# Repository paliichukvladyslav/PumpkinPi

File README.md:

# Pumpkin Pi

A small Linux single-board computer based on the Allwinner V3s.

## Hardware Specifications

| Component | Specification |
|---|---|
| SoC | Allwinner V3s (eLQFP-128) |
| CPU | Single-core ARM Cortex-A7, up to 1.2 GHz (typically 1.008 GHz) |
| RAM | 64 MiB DDR2, 400 MHz, integrated into the SoC |
| PMIC | X-Powers AXP202 |
| Power rails | 1.2V (CPU/System), 3.3V (I/O), 3.0V (Analog) |
| DDR2 power supply | 1.8V via dedicated SY8088AAC regulator |
| Flash storage | 16 MiB Winbond W25Q128JVFIQ SPI NOR (SPI0) |
| Main oscillator | 24 MHz crystal, ±10 ppm, 12 pF |
| RTC oscillator | 32.768 kHz crystal, ±20 ppm, 12.5 pF |
| Power input | USB Type-C (16-pin connector, power only) |
| Serial interfaces | UART0, UART2 |
| GPIO | 6 exposed GPIO pins (PE19–PE24) |
| Programming | Dedicated SPI NOR programming header |
| Status LED | White LED with Linux heartbeat support |
| Fan connector | 2-pin JST-PH, 3.3V |
| PCB | 4 layers, 49.9 × 45 mm |

## Software

Firmware and Linux support are yet to be implemented.

## Project Files

The repository contains the KiCad schematic, PCB layout, custom symbols, footprints, and 3D models.

If KiCad reports a missing `PumpkinPi` footprint library, reconnect `PumpkinPi.pretty` through **Preferences → Manage Footprint Libraries**.

## License

The Pumpkin Pi hardware design is licensed under
[CC BY-SA 4.0](https://creativecommons.org/licenses/by-sa/4.0/).

See Third-Party Credits for attribution of reused and adapted designs.

## Third-Party Credits

This project is partially based on and inspired by the [FunKey S Hardware](https://github.com/FunKey-Project/FunKey-S-Hardware) project.

The following elements were reused or adapted from its hardware design:

- KiCad schematic symbols for the Allwinner V3s and AXP20x PMIC.
- Crystal oscillator circuits (24 MHz and 32.768 kHz).
- SVREF reference voltage circuitry.
- DDR2 power supply design using the SY8088 regulator.
- General power management and schematic design concepts.

The original FunKey S hardware design is licensed under [CC BY-SA 4.0](https://creativecommons.org/licenses/by-sa/4.0/). Components and circuits reused in Pumpkin Pi have been adapted for this board.

Credit goes to the FunKey Project contributors for making their hardware design publicly available.

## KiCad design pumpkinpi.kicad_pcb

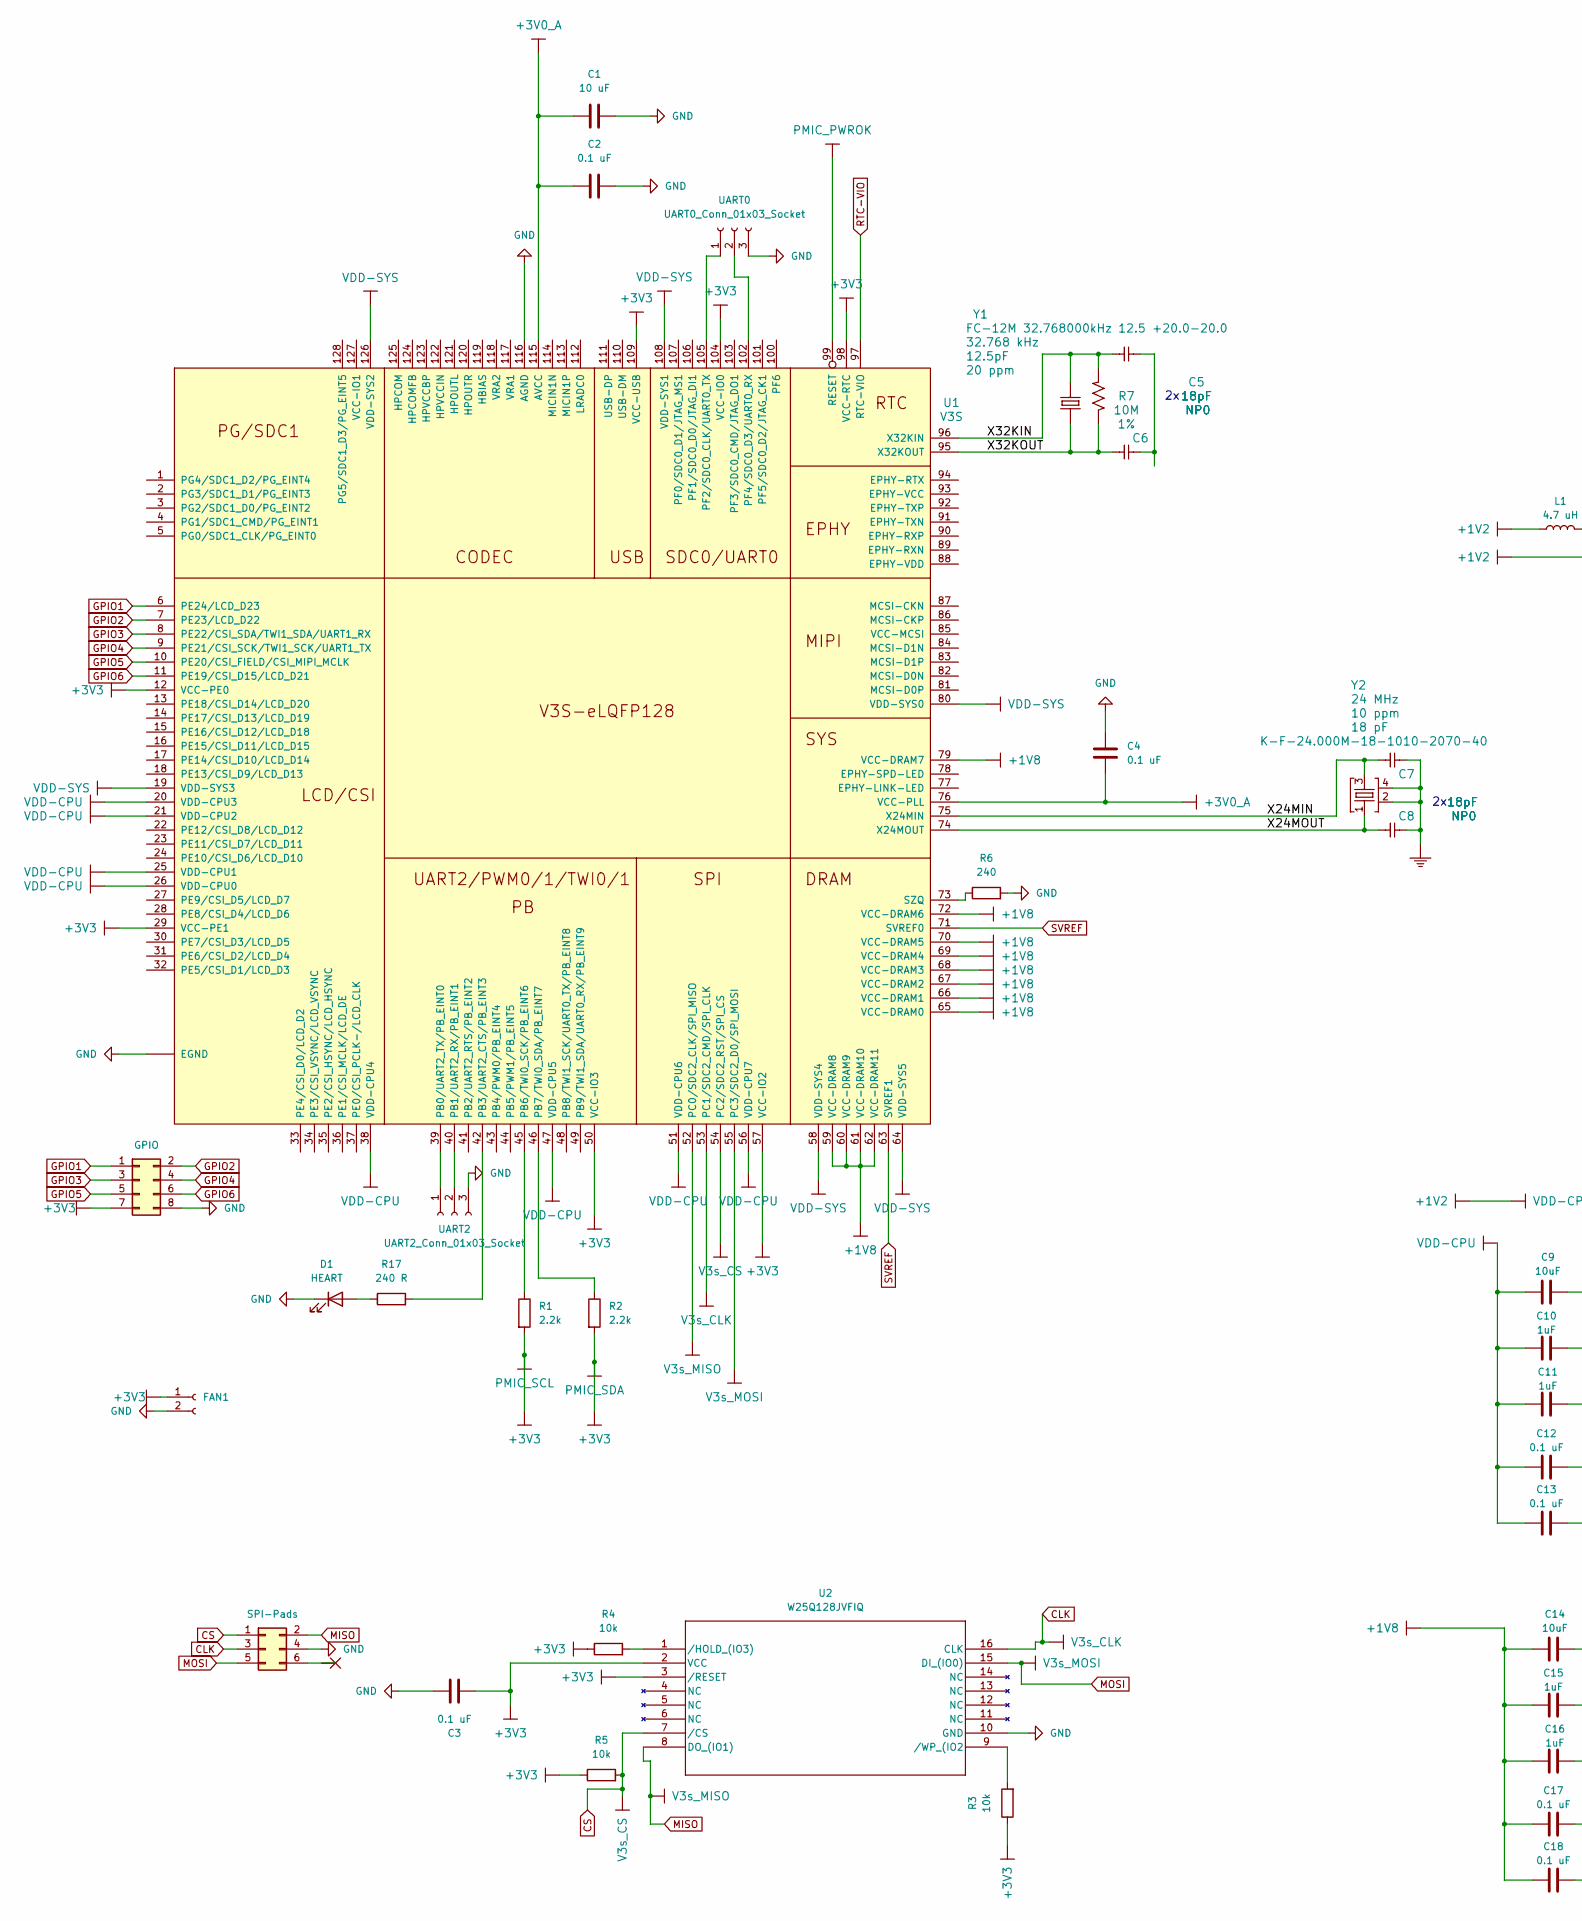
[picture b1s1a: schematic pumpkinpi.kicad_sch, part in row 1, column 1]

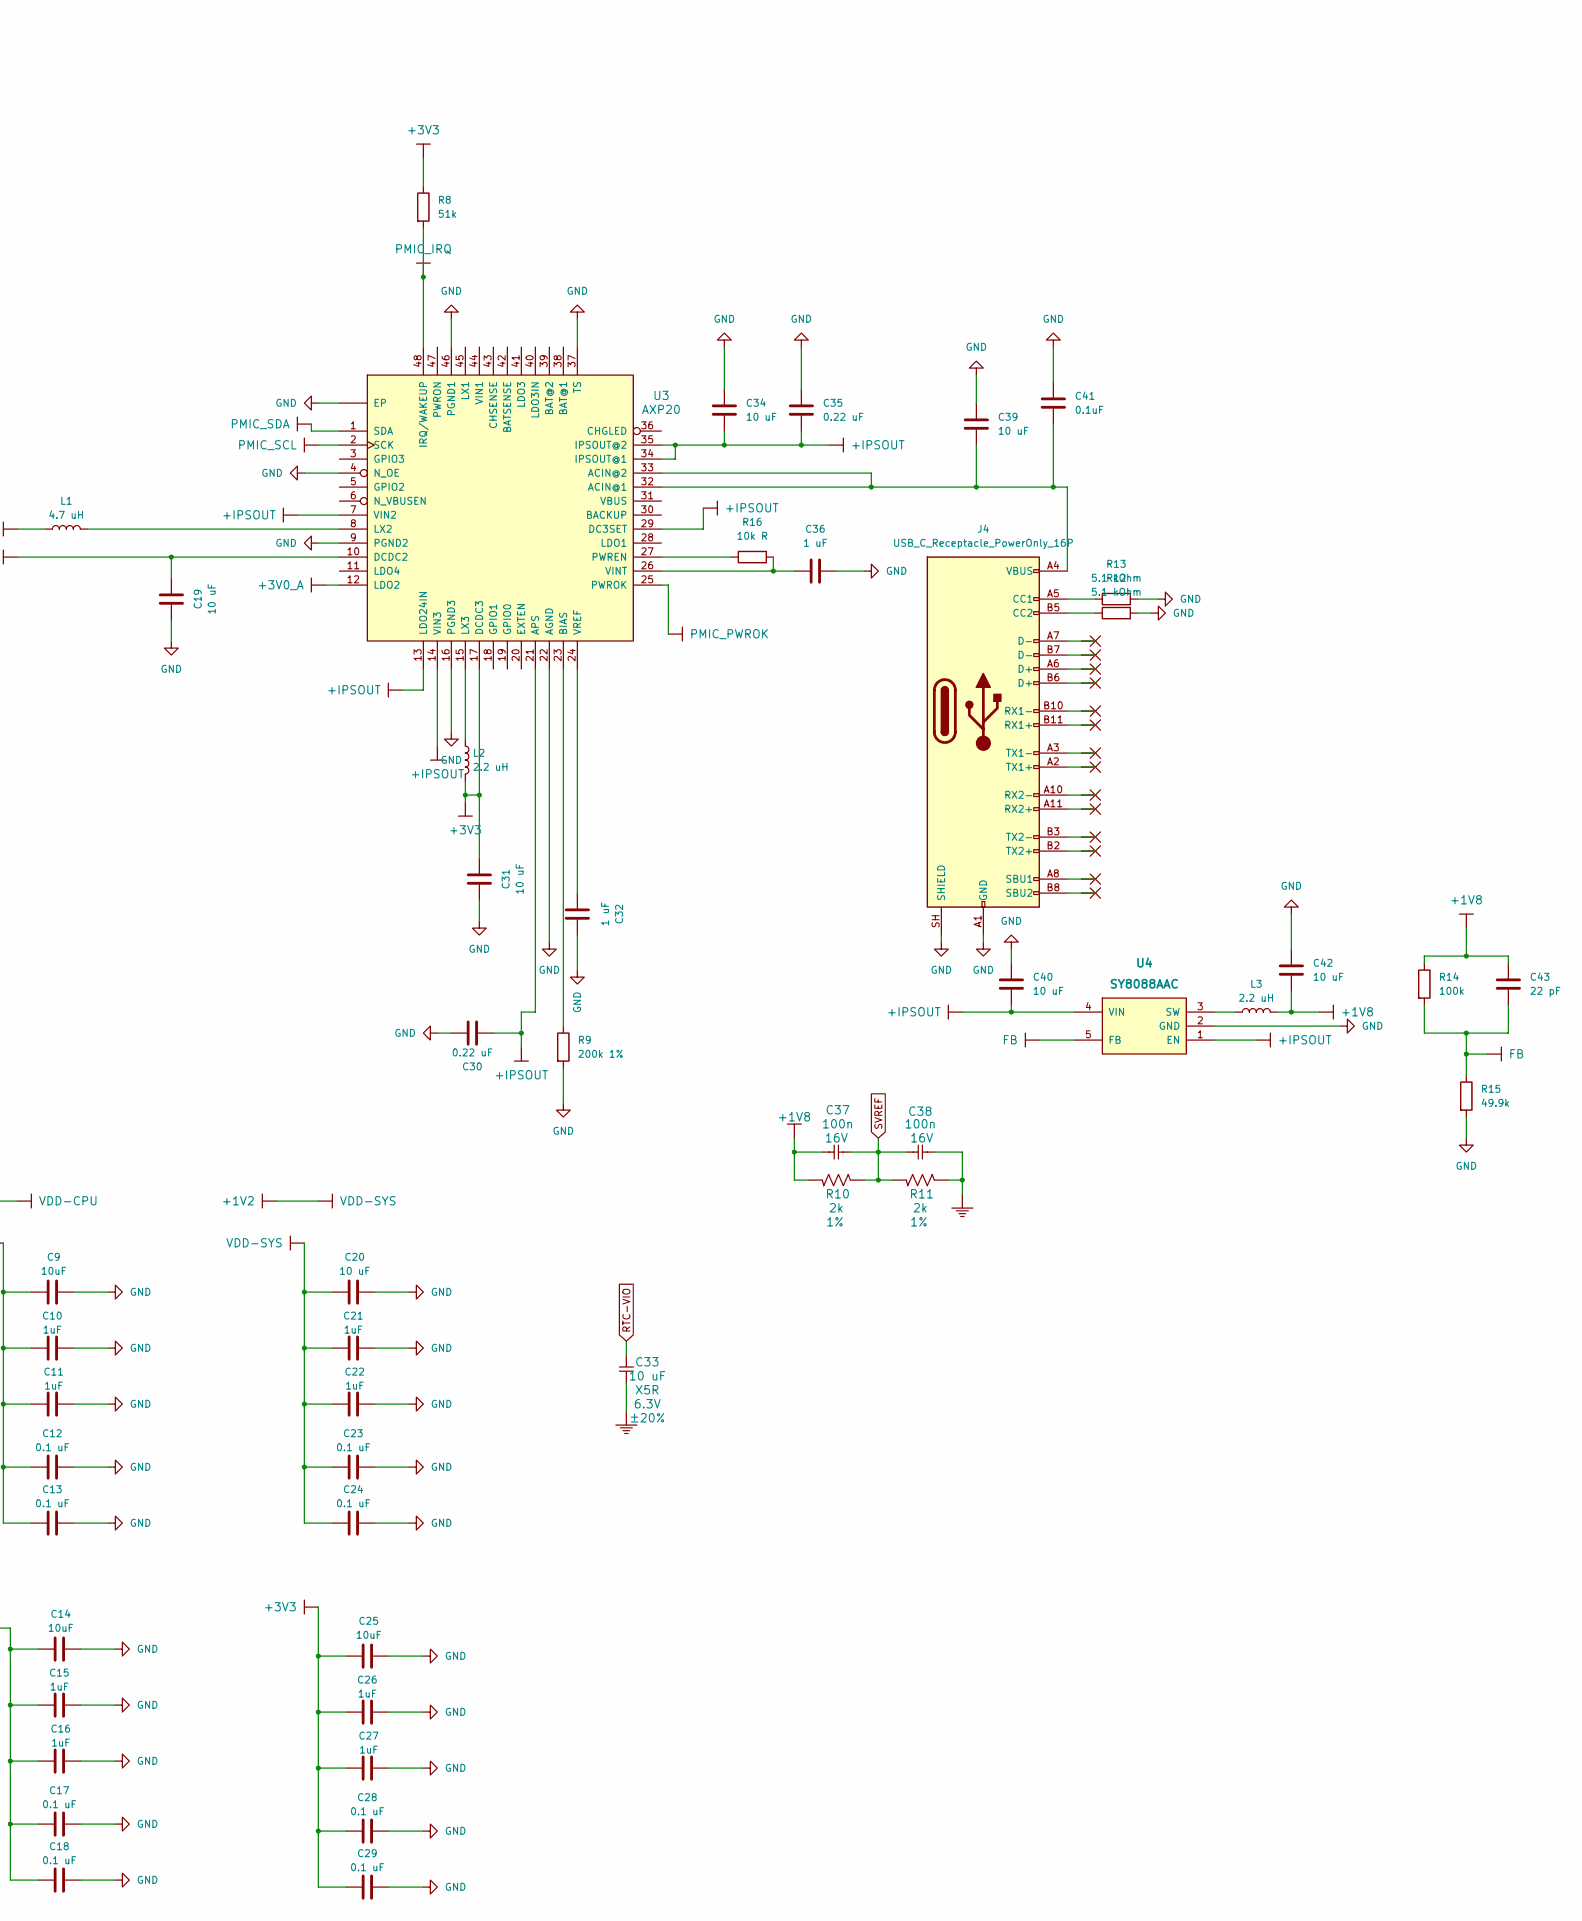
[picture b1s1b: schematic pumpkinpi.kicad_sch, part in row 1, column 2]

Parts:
C1, C19, C20, C31, C34, C39, C40, C42: 10 uF; C_0805_2012Metric
C2, C3, C4, C12, C13, C17, C18, C23, C24, C28, C29: 0.1 uF; C_0603_1608Metric
C5, C6, C7, C8: 18pF; C_0603_1608Metric; PARTNO C0402_18p_NP0_5%_CER_50V
C9: 10uF; C_0603_1608Metric
C10, C11, C15, C16, C21, C22, C26, C27: 1uF; C_0603_1608Metric
C14, C25: 10uF; C_0805_2012Metric
C30, C35: 0.22 uF; C_0603_1608Metric
C32, C36: 1 uF; C_0603_1608Metric
C33: 10 uF; C_0805_2012Metric; PARTNO C0402_10u_X5R_20%_CER_6V3
C37, C38: 100n; C_0603_1608Metric; PARTNO C0402_100n_X7R_10%_CER_16V
C41: 0.1uF; C_0603_1608Metric
C43: 22 pF; C_0603_1608Metric
D1: HEART; SUPER_BRIGHT_SMD_LED_3014
FAN1: Conn_01x02_Socket; JST_PH_B2B-PH-K_1x02_P2.00mm_Vertical
J1: GPIO; PinSocket_2x04_P2.54mm_Vertical
J4: USB_C_Receptacle_PowerOnly_16P; USB_C_Receptacle_GCT_USB4110
L1: 4.7 uH; IND_EPCOS_B82462G4_EPC
L2, L3: 2.2 uH; IND_CDRH2D14NP-2R2NC_SUM
R1, R2: 2.2k; R_0603_1608Metric
R3, R4, R5: 10k; R_0603_1608Metric
R6: 240; R_0603_1608Metric
R7: 10M; R_0603_1608Metric; PARTNO R0402_10M_1%_62.5mW
R8: 51k; R_0603_1608Metric
R9: 200k 1%; R_0603_1608Metric
R10, R11: 2k; R_0603_1608Metric; PARTNO R0402_2k_1%_62.5mW
R12, R13: 5.1 kOhm; R_0603_1608Metric
R14: 100k; R_0603_1608Metric
R15: 49.9k; R_0603_1608Metric
R16: 10k R; R_0603_1608Metric
R17: 240 R; R_0603_1608Metric
SPI-Pads1: SPI-Pads; PinHeader_1x05_P2.54mm_Vertical
U1: V3S; ELQFP-128
U2: W25Q128JVFIQ; SOIC_28JVFIQ_WIN
U3: AXP20; QFN48
U4: SY8088AAC; SOT23-5
UART0: UART0_Conn_01x03_Socket; PinSocket_1x03_P2.54mm_Vertical
UART2: UART2_Conn_01x03_Socket; PinSocket_1x03_P2.54mm_Vertical
Y1: FC-12M 32.768000kHz 12.5 +20.0-20.0; FC-12M; PARTNO FC-12M_32K768_12.5PF_20PPM
Y2: K-F-24.000M-18-1010-2070-40; CRYSTAL_32X25; PARTNO XTAL3225_4P_24M_18PF_10PPM

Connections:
+1V2: C9.2, C10.2, C11.2, C12.2, C13.2, C19.2, C20.2, C21.2, C22.2, C23.2, C24.2, L1.1, U1.19 (VDD-SYS3), U1.20 (VDD-CPU3), U1.21 (VDD-CPU2), U1.25 (VDD-CPU1), U1.26 (VDD-CPU0), U1.38 (VDD-CPU4), U1.47 (VDD-CPU5), U1.51 (VDD-CPU6), U1.56 (VDD-CPU7), U1.58 (VDD-SYS4), U1.64 (VDD-SYS5), U1.80 (VDD-SYS0), U1.108 (VDD-SYS1), U1.126 (VDD-SYS2), U3.10 (DCDC2)
+1V8: C14.2, C15.2, C16.2, C17.2, C18.2, C37.2, C42.2, C43.1, L3.2, R10.2, R14.1, U1.59 (VCC-DRAM8), U1.60 (VCC-DRAM9), U1.61 (VCC-DRAM10), U1.62 (VCC-DRAM11), U1.65 (VCC-DRAM0), U1.66 (VCC-DRAM1), U1.67 (VCC-DRAM2), U1.68 (VCC-DRAM3), U1.69 (VCC-DRAM4), U1.70 (VCC-DRAM5), U1.72 (VCC-DRAM6), U1.79 (VCC-DRAM7)
+3V0_A: C1.1, C2.1, C4.2, U1.76 (VCC-PLL), U1.115 (AVCC), U3.12 (LDO2)
+3V3: C3.1, C25.2, C26.2, C27.2, C28.2, C29.2, C31.2, FAN1.1, J1.7, L2.2, R1.2, R2.2, R3.1, R4.1, R5.1, R8.1, U1.12 (VCC-PE0), U1.29 (VCC-PE1), U1.50 (VCC-IO3), U1.57 (VCC-IO2), U1.98 (VCC-RTC), U1.104 (VCC-IO0), U1.109 (VCC-USB), U2.2 (VCC), U2.3 (/RESET), U3.1 (SDA), U3.2 (SCK), U3.17 (DCDC3)
+IPSOUT: C30.1, C34.2, C35.2, C40.2, U3.7 (VIN2), U3.13 (LDO24IN), U3.14 (VIN3), U3.21 (APS), U3.29 (DC3SET), U3.34 (IPSOUT@1), U3.35 (IPSOUT@2), U4.1 (EN), U4.4 (VIN)
/X24MIN: C7.2, U1.75 (X24MIN), Y2.3
/X24MOUT: C8.2, U1.74 (X24MOUT), Y2.1
/X32KIN: C5.2, R7.2, U1.96 (X32KIN), Y1.2
/X32KOUT: C6.2, R7.1, U1.95 (X32KOUT), Y1.1
CLK: SPI-Pads1.3, U1.53 (PC1/SDC2_CMD/SPI_CLK), U2.16 (CLK)
CS: R5.2, SPI-Pads1.1, U1.54 (PC2/SDC2_RST/SPI_CS), U2.7 (/CS)
FB: C43.2, R14.2, R15.1, U4.5 (FB)
GND: C1.2, C2.2, C3.2, C4.1, C7.1, C8.1, C9.1, C10.1, C11.1, C12.1, C13.1, C14.1, C15.1, C16.1, C17.1, C18.1, C19.1, C20.1, C21.1, C22.1, C23.1, C24.1, C25.1, C26.1, C27.1, C28.1, C29.1, C30.2, C31.1, C32.2, C33.2, C34.1, C35.1, C36.2, C38.1, C39.2, C40.1, C41.2, C42.1, D1.1 (K), FAN1.2, J1.8, J4.A1 (GND), J4.A12 (GND), J4.B1 (GND), J4.B12 (GND), J4.SH (SHIELD), R6.2, R9.2, R11.1, R12.2, R13.2, R15.2, SPI-Pads1.4, U1.116 (AGND), U1.GND$1 (EGND), U1.GND$2 (EGND), U1.GND$3 (EGND), U1.GND$4 (EGND), U1.GND$5 (EGND), U1.GND$6 (EGND), U1.GND$7 (EGND), U1.GND$8 (EGND), U1.GND$9 (EGND), U2.10 (GND), U3.4 (N_OE), U3.9 (PGND2), U3.16 (PGND3), U3.22 (AGND), U3.37 (TS), U3.46 (PGND1), U3.GND$1 (EP), U3.GND$2 (EP), U3.GND$3 (EP), U3.GND$4 (EP), U3.GND$5 (EP), U3.GND$6 (EP), U3.GND$7 (EP), U3.GND$8 (EP), U3.GND$9 (EP), U4.2 (GND), UART0.3, UART2.3, Y2.2, Y2.4
GPIO1: J1.1, U1.6 (PE24/LCD_D23)
GPIO2: J1.2, U1.7 (PE23/LCD_D22)
GPIO3: J1.3, U1.8 (PE22/CSI_SDA/TWI1_SDA/UART1_RX)
GPIO4: J1.4, U1.9 (PE21/CSI_SCK/TWI1_SCK/UART1_TX)
GPIO5: J1.5, U1.10 (PE20/CSI_FIELD/CSI_MIPI_MCLK)
GPIO6: J1.6, U1.11 (PE19/CSI_D15/LCD_D21)
MISO: SPI-Pads1.2, U1.52 (PC0/SDC2_CLK/SPI_MISO), U2.8 (DO_(IO1))
MOSI: SPI-Pads1.5, U1.55 (PC3/SDC2_D0/SPI_MOSI), U2.15 (DI_(IO0))
unnamed: C5.1, C6.1
unnamed: D1.2 (A), R17.1
unnamed: J4.A5 (CC1), R13.1
unnamed: J4.B5 (CC2), R12.1
unnamed: U1.39 (PB0/UART2_TX/PB_EINT0), UART2.1
unnamed: U1.40 (PB1/UART2_RX/PB_EINT1), UART2.2
unnamed: R17.2, U1.42 (PB3/UART2_CTS/PB_EINT3)
unnamed: R1.1, U1.45 (PB6/TWI0_SCK/PB_EINT6)
unnamed: R2.1, U1.46 (PB7/TWI0_SDA/PB_EINT7)
unnamed: U1.105 (PF2/SDC0_CLK/UART0_TX), UART0.1
unnamed: U1.102 (PF4/SDC0_D3/UART0_RX), UART0.2
unnamed: R6.1, U1.73 (SZQ)
unnamed: R4.2, U2.1 (/HOLD_(IO3))
unnamed: R3.2, U2.9 (/WP_(IO2)
unnamed: C39.1, C41.1, J4.A4 (VBUS), J4.A9 (VBUS), J4.B4 (VBUS), J4.B9 (VBUS), U3.32 (ACIN@1), U3.33 (ACIN@2)
unnamed: R9.1, U3.23 (BIAS)
unnamed: L1.2, U3.8 (LX2)
unnamed: L2.1, U3.15 (LX3)
unnamed: R16.1, U3.27 (PWREN)
unnamed: C36.1, R16.2, U3.26 (VINT)
unnamed: C32.1, U3.24 (VREF)
unnamed: L3.1, U4.3 (SW)
PMIC_IRQ: R8.2, U3.48 (IRQ/WAKEUP)
PMIC_PWROK: U1.99 (RESET), U3.25 (PWROK)
RTC-VIO: C33.1, U1.97 (RTC-VIO)
SVREF: C37.1, C38.2, R10.1, R11.2, U1.63 (SVREF1), U1.71 (SVREF0)

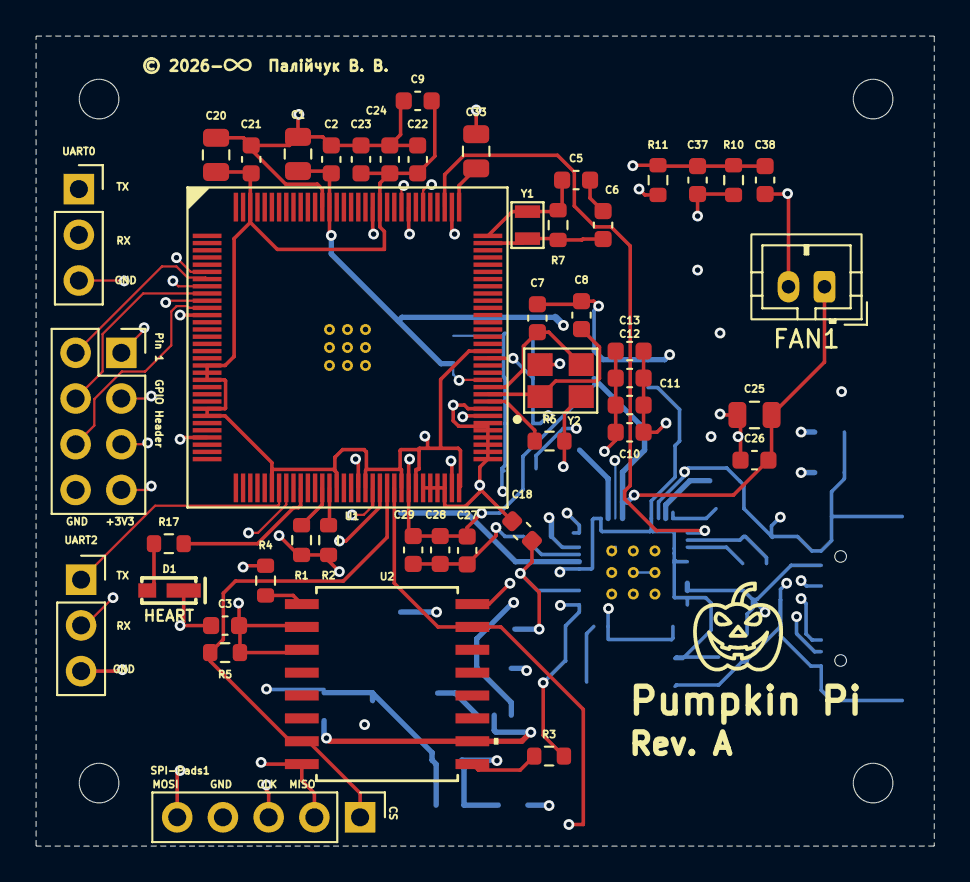
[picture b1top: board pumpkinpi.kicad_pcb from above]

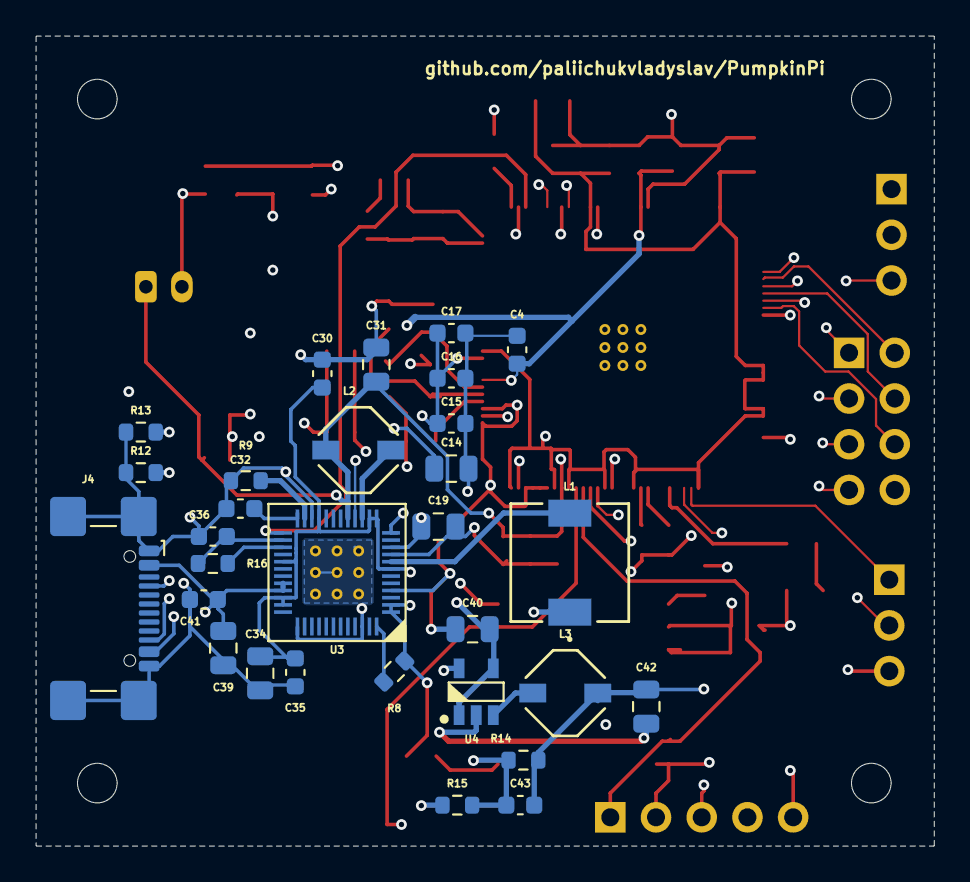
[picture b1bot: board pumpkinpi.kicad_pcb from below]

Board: 4 copper layers, 49.9 x 45.0 mm, 76 parts (30 on the bottom side), 47 nets.

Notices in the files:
pumpkinpi.kicad_pcb:
© 2026-
